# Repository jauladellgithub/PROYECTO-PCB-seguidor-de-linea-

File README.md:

# PROYECTO-PCB-seguidor-de-linea-
Robot seguidor de linea

Finalmente hoy 25-11 la placa de nuestro robot seguidor de linea esta terminado
nos tomo un proceso de 3 etapas para llegar finalmente a nuestra placa terminada
esperamos que no haya ningun problema con este proyecto en un futuro
tambien queremos agredecer a nuestro profesor CRISTOBAL NETTLE.
por los conocimientos entregados durante este periodo
y a los compañeros por enseñarnos sus trabajos y asi aprender mas sobre
el diseño de placas PCB

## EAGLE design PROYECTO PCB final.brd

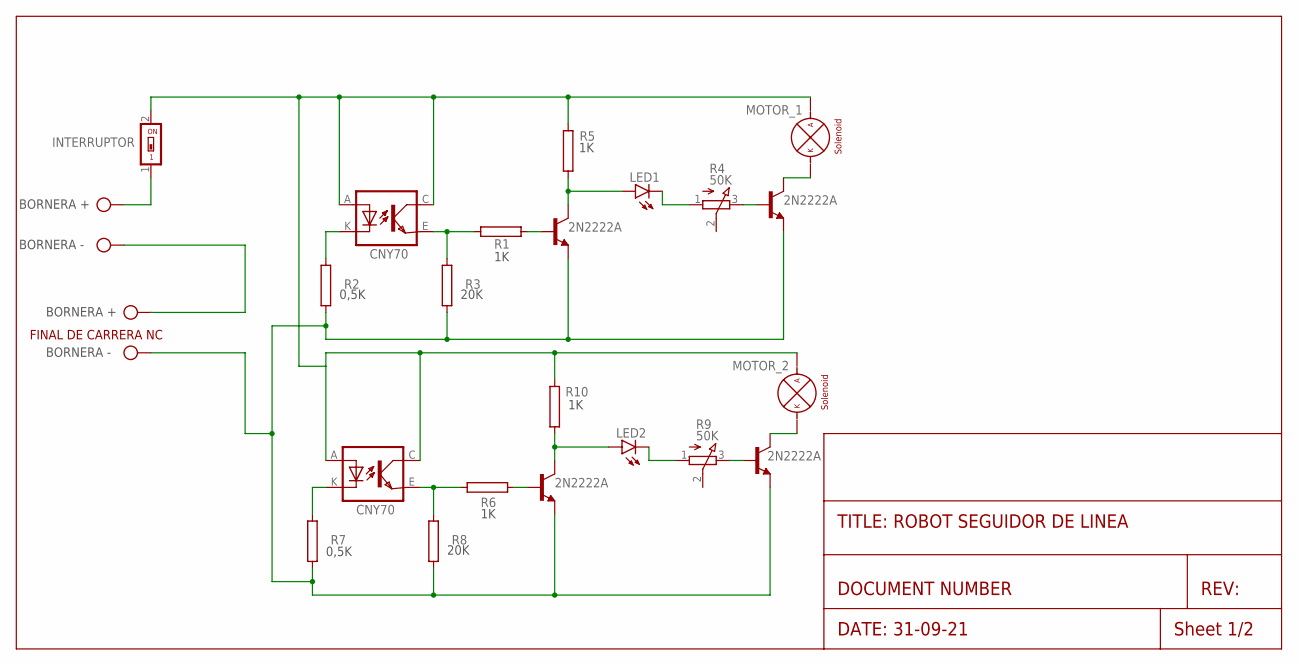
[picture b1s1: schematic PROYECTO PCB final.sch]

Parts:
BORNERA_+, BORNERA_+1: AK300/2
INTERRUPTOR: SWS001; SMS-001
LED1, LED2: TLLY4400; LED3MM
MOTOR_1, MOTOR_2: -MOTOR; CON2
Q1, Q2, Q3, Q4: 2N2222A; TO18
R1, R2, R3, R5, R6, R7, R8, R10: RMG100-V; TO-247-2V
R4, R9: 50K; 3RP/1610N
U$1, U$3: CNY70; 4

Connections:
unnamed: R2.2, U$1.K (C)
unnamed: BORNERA_+.1, INTERRUPTOR.1
unnamed: Q1.2 (B), R1.2
unnamed: R1.1, R3.2, U$1.E (EMI)
unnamed: LED1.A, Q1.3 (C), R5.1
unnamed: LED1.K (C), R4.1 (A)
unnamed: Q2.2 (B), R4.3 (E)
unnamed: MOTOR_1.P$2 (-), Q2.3 (C)
unnamed: Q3.2 (B), R6.2
unnamed: R6.1, R8.2, U$3.E (EMI)
unnamed: R7.2, U$3.K (C)
unnamed: LED2.A, Q3.3 (C), R10.1
unnamed: LED2.K (C), R9.1 (A)
unnamed: Q4.2 (B), R9.3 (E)
unnamed: MOTOR_2.P$2 (-), Q4.3 (C)
unnamed: INTERRUPTOR.2, MOTOR_1.P$1 (+), MOTOR_2.P$1 (+), R5.2, R10.2, U$1.A, U$1.C (COL), U$3.A, U$3.C (COL)
unnamed: BORNERA_+.2, BORNERA_+1.1
unnamed: BORNERA_+1.2, Q1.1 (E), Q2.1 (E), Q3.1 (E), Q4.1 (E), R2.1, R3.1, R7.1, R8.1

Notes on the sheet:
TITLE: ROBOT SEGUIDOR DE LINEA
DATE: 31-09-21
REV:
Sheet 1/2
DOCUMENT NUMBER
0,5K
20K
BORNERA +
BORNERA -
FINAL DE CARRERA NC

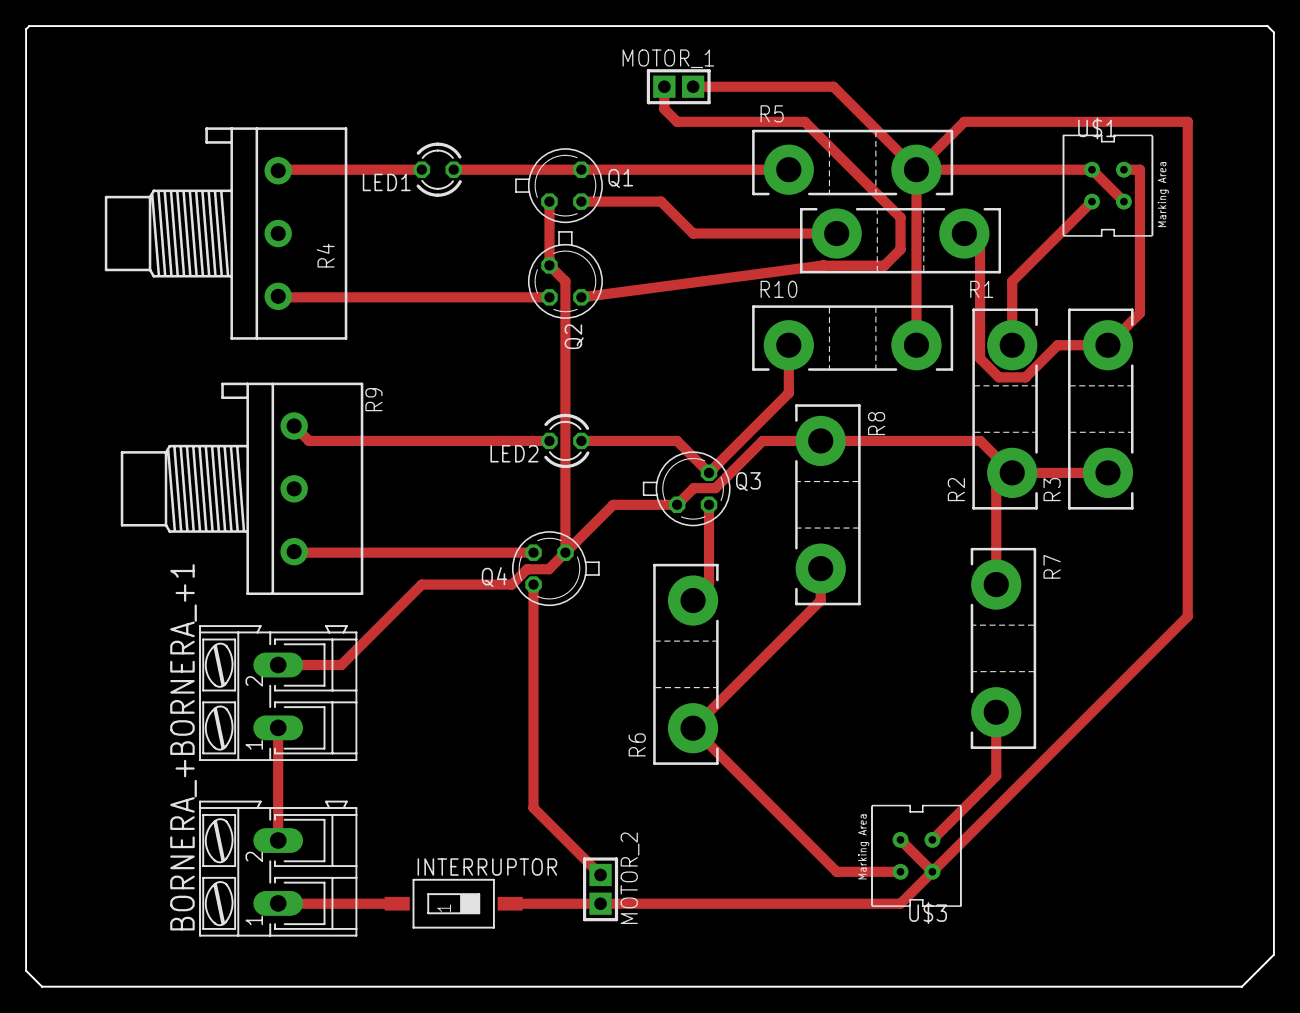
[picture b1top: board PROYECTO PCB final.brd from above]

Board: 2 copper layers, 99.3 x 76.5 mm, 23 parts (0 on the bottom side), 18 nets.
